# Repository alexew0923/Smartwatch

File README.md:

# Smartch
This repository contains all the files for the smartwatch and it is participating in the Stardance Challenge by Hack Club.

## Demo Video

# Bill of Materials
Components are bought from DigiKey, AliExpress and Amazon.
For more information, refer to the excel file under KiCad.
- XIAO ESP32C3 (main processor)
- 450mAh LiPo Battery with PH 2.0 mm JST Connector
- PH 2.0 mm JST Connector
- 4 x 100nF 0603_1608 Capacitors (DigiKey part number: 1276-1005-1-ND)
- 1.28 inch Round TFT Display (with pin sockets)
- DS3231 RTC Module (with pin headers)
- 6 x 10k 0603_1608 Resistors (DigiKey part number: 311-10.0KHRCT-ND)
- 4 x 4.7k 0603_1608 Resistors (DigiKey part number: 311-4.70KHRCT-ND)
- 2 x Tactile Switches (DigiKey part number: P10851SCT-ND)
- SMD SHT40 Temp&Hum Sensor (DigiKey part number: 1649-SHT40-AD1F-R2CT-ND)
- SMD VEML6035 Ambient Light Sensor (DigiKey part number: VEML6035CT-ND)
- MPU6050 (with pin sockets)
- SMD BMP581 Air Pressure Sensor (DigiKey part number: 828-BMP581CT-ND)
- SMD CPT-9019A-SMT-TR Passive Buzzer (DigiKey part number: 2223-CPT-9019A-SMT-TRCT-ND)

The total cost is 49.45 CAD.

## KiCad Designs
## Schematic

## PCB
I used JLCPCB, but you can you any other PCB fabrication services. I selected 1.6 mm white PCB. If want to solder components by yourself rather than assembly option, order a stencil and solder paste as well. When soldering the battery connector, double check the polarity!
There are schematic and PCB file under KiCad, so feel free to modify it or if you would like to order it right away, download Smartwatch.zip file which contains gerber files and upload it onto PCB manufacture's website.

## Case Design
I 3D printed a case designed on SolidWorks. The PCB sits on the base of the case and the lid snaps into the body. When you are modifying the SolidWorks file, be careful because I am using a student version, so it will leave a watermark. If you would like to 3D print it, you can use the STL file instead.

# Core Feature
This smartwatch uses LVGL graphics library to develop user interface.

## Current Features
1. Uses DS3231 RTC module, keeping time reliably even when the battery is dead.
2. Basic features in a clock app, such as stopwatch, timer and time adjustment.
3. Uses SHT40 sensor to log temperature on a graph.
4. Accelerometer & gyroscope readings and visualization using MPU6050.
5. Air pressure and altitude readings from BMP581.

## Features for Future Version
1. Connect to the phone via Bluetooth to receive data such as weather, message, and news.
2. Battery voltage reading

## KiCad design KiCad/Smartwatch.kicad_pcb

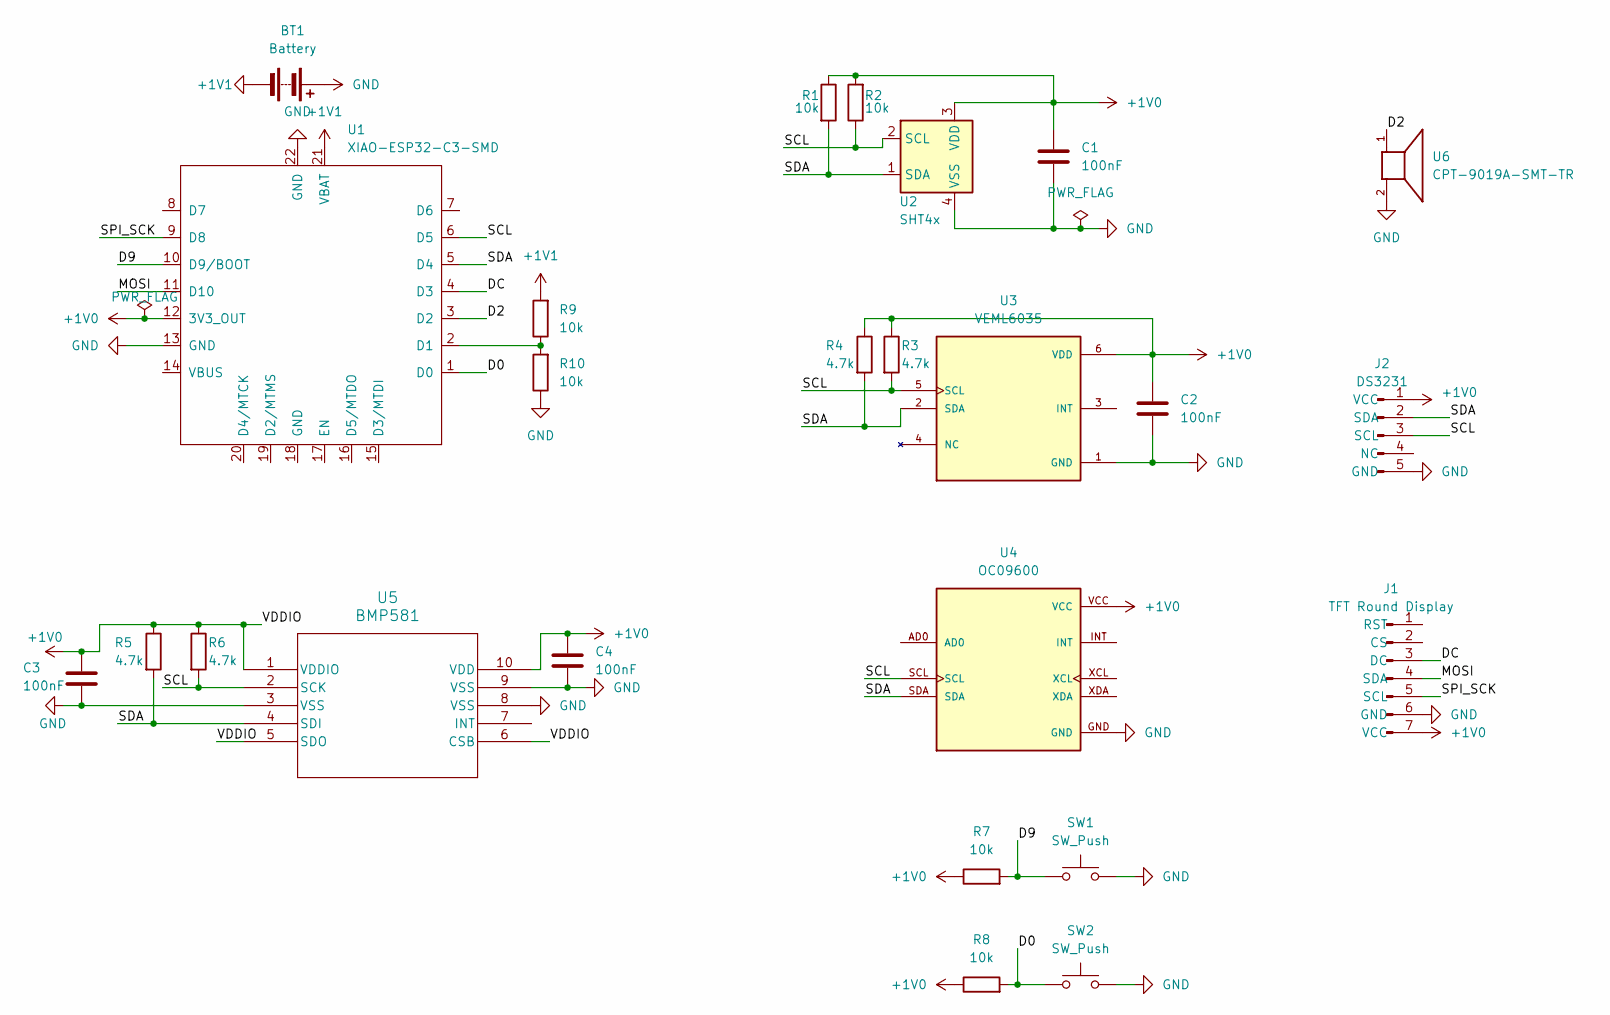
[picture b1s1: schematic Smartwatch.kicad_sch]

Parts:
BT1: Battery; JST_PH_S2B-PH-K_1x02_P2.00mm_Horizontal
C1, C2, C3, C4: 100nF; C_0603_1608Metric
J1: TFT Round Display; PinSocket_1x07_P2.54mm_Vertical
J2: DS3231; PinHeader_1x05_P2.54mm_Vertical
R1, R2, R7, R8, R9, R10: 10k; R_0603_1608Metric
R3, R4, R5, R6: 4.7k; R_0603_1608Metric
SW1, SW2: SW_Push; Panasonic_EVQPUJ_EVQPUA
U1: XIAO-ESP32-C3-SMD
U2: SHT4x; Sensirion_DFN-4_1.5x1.5mm_P0.8mm_SHT4x_NoCentralPad
U3: VEML6035; XDCR_VEML6035; PARTREV 1.3
U4: OC09600; MODULE_OC09600; PARTREV NA
U5: BMP581; QFN10_BMP581_BOS
U6: CPT-9019A-SMT-TR; XDCR_CPT-9019A-SMT-TR; PARTREV 1.02

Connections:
+1V0: C1.1, C2.1, C3.1, C4.1, J1.7 (VCC), J2.1 (VCC), R1.1, R2.2, R3.1, R4.1, R5.1, R6.1, R7.1, R8.1, U1.12 (3V3_OUT), U2.3 (VDD), U3.6 (VDD), U4.VCC, U5.1 (VDDIO), U5.5 (SDO), U5.6 (CSB), U5.10 (VDD)
+1V1: BT1.2 (-), R9.2, U1.21 (VBAT)
/D0: R8.2, SW2.1, U1.1 (D0)
/D2: U1.3 (D2), U6.1
/D9: R7.2, SW1.1, U1.10 (D9/BOOT)
/DC: J1.3 (DC), U1.4 (D3)
/MOSI: J1.4 (SDA), U1.11 (D10)
/SCL: J2.3 (SCL), R2.1, R3.2, R6.2, U1.6 (D5), U2.2 (SCL), U3.5 (SCL), U4.SCL, U5.2 (SCK)
/SDA: J2.2 (SDA), R1.2, R4.2, R5.2, U1.5 (D4), U2.1 (SDA), U3.2 (SDA), U4.SDA, U5.4 (SDI)
/SPI_SCK: J1.5 (SCL), U1.9 (D8)
GND: BT1.1 (+), C1.2, C2.2, C3.2, C4.2, J1.6 (GND), J2.5 (GND), R10.1, SW1.2, SW2.2, U1.13 (GND), U1.22 (GND), U2.4 (VSS), U3.1 (GND), U4.GND, U5.3 (VSS), U5.8 (VSS), U5.9 (VSS), U6.2
unnamed: R9.1, R10.2, U1.2 (D1)

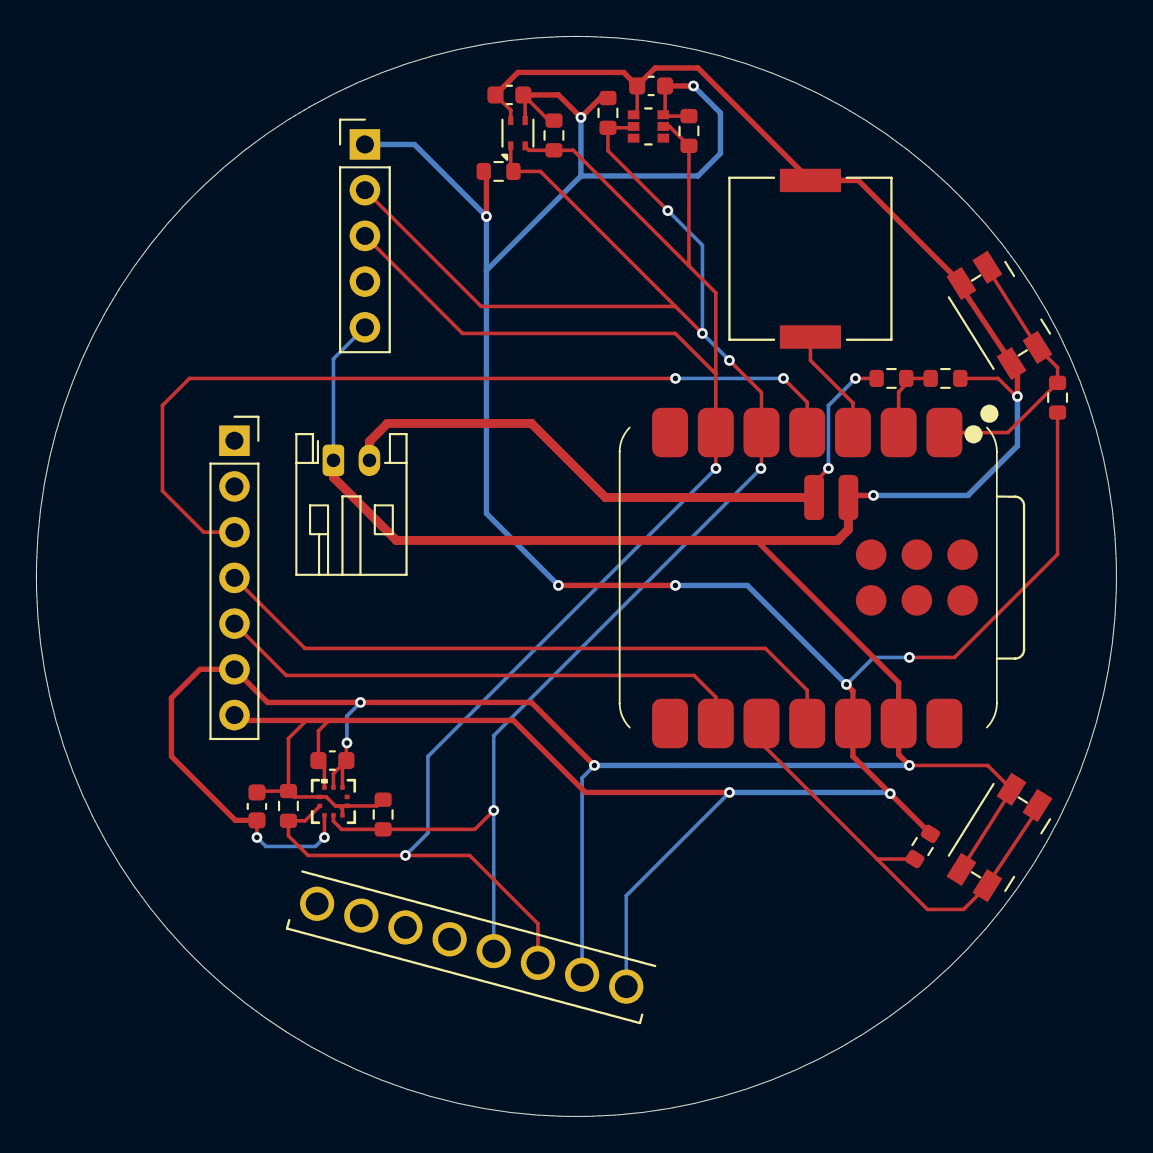
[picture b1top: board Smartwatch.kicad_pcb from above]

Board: 2 copper layers, 60.0 x 60.0 mm, 25 parts (0 on the bottom side), 12 nets.
